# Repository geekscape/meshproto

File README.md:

meshproto
=========

MeshProto module: Hardware and software repository.

About:

Prototyping board with mounting points and pinouts to match MeshThing and MeshUSB.

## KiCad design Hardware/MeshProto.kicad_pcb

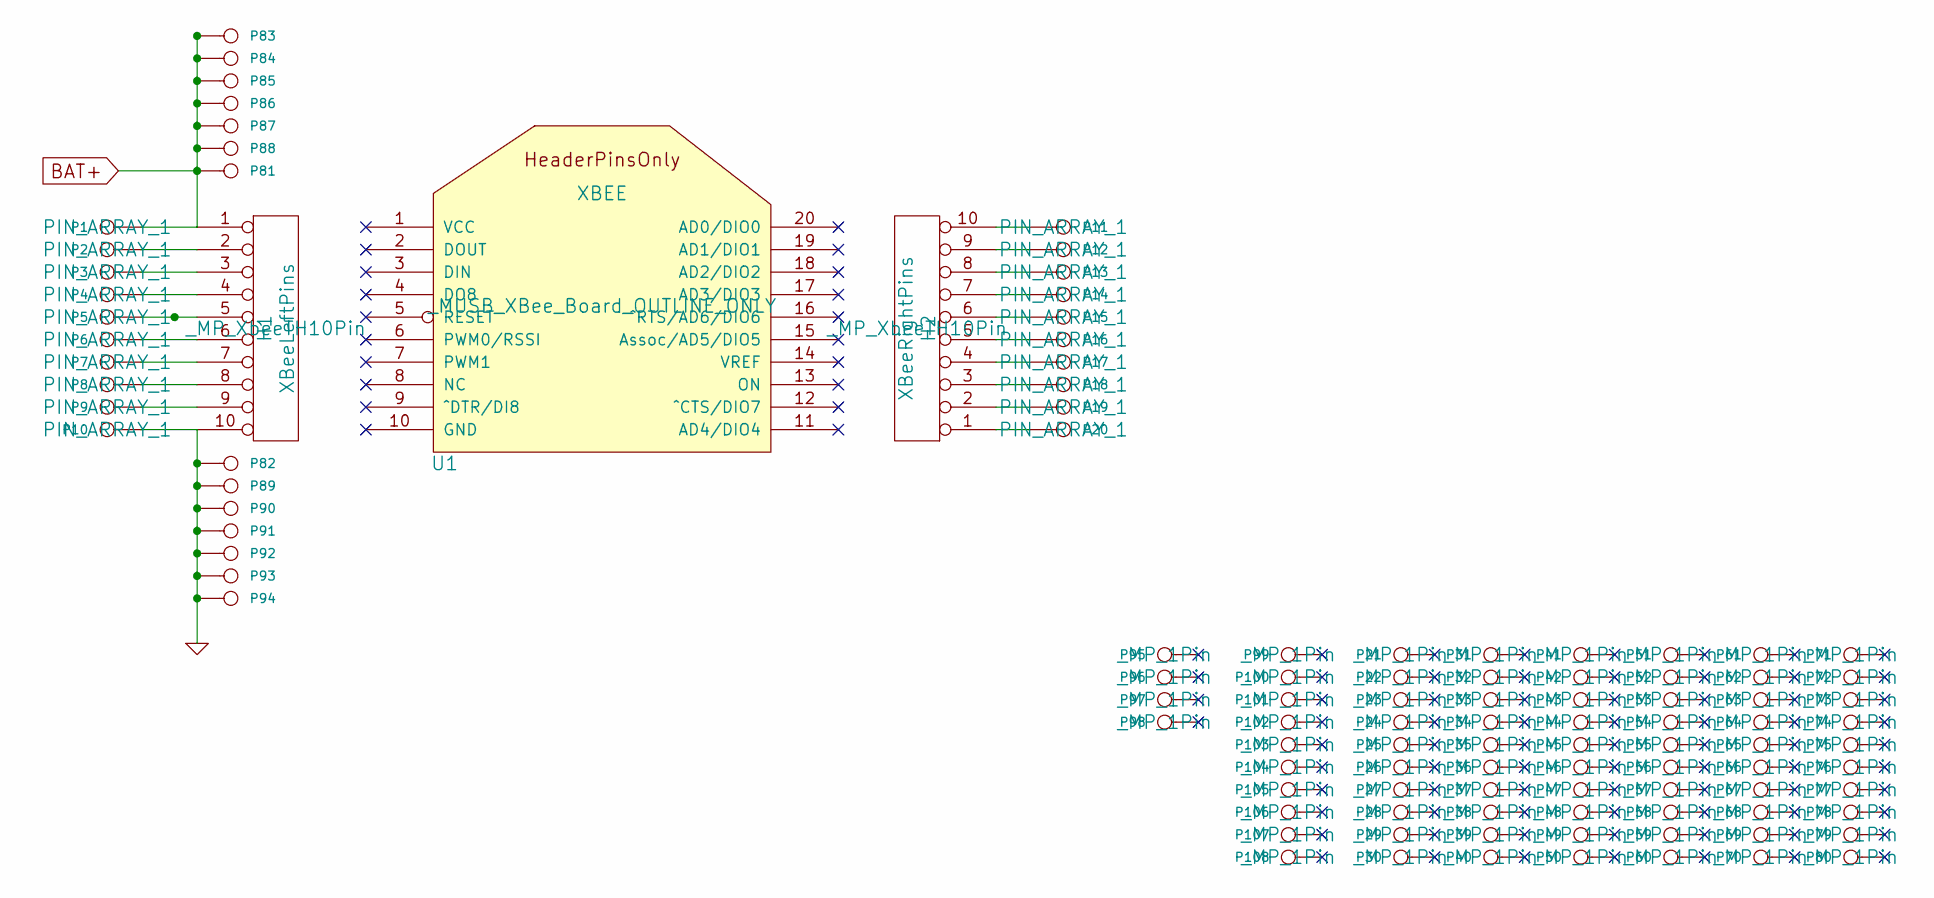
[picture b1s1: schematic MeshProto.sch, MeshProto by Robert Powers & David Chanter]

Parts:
H1: XBeeLeftPins; _MP_XbeeTH10Pin
H2: XBeeRightPins; _MP_XbeeTH10Pin
P1, P2, P3, P4, P5, P6, P7, P8, P9, P10, P11, P12, P13, P14, P15, P16, P17, P18, P19, P20: CONN_1; PIN_ARRAY_1
P21, P22, P23, P24, P25, P26, P27, P28, P29, P30, P31, P32, P33, P34, P35, P36, P37, P38, P39, P40, P41, P42, P43, P44, P45, P46, P47, P48, P49, P50, P51, P52, P53, P54, P55, P56, P57, P58, P59, P60, P61, P62, P63, P64, P65, P66, P67, P68, P69, P70, P71, P72, P73, P74, P75, P76, P77, P78, P79, P80, P95, P96, P97, P98, P99, P100, P101, P102, P103, P104, P105, P106, P107, P108: CONN_1; _MP_1Pin
P81, P82, P83, P84, P85, P86, P87, P88, P89, P90, P91, P92, P93, P94: CONN_1
U1: XBEE; _MUSB_XBee_Board_OUTLINE_ONLY

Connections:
BAT+: H1.1, P1.1, P81.1, P83.1, P84.1, P85.1, P86.1, P87.1, P88.1
GND: H1.10, P10.1, P82.1, P89.1, P90.1, P91.1, P92.1, P93.1, P94.1
unnamed: H1.2, P2.1
unnamed: H1.3, P3.1
unnamed: H1.4, P4.1
unnamed: H1.5, P5.1
unnamed: H1.6, P6.1
unnamed: H1.7, P7.1
unnamed: H1.8, P8.1
unnamed: H1.9, P9.1
unnamed: H2.1, P20.1
unnamed: H2.2, P19.1
unnamed: H2.3, P18.1
unnamed: H2.4, P17.1
unnamed: H2.5, P16.1
unnamed: H2.6, P15.1
unnamed: H2.7, P14.1
unnamed: H2.8, P13.1
unnamed: H2.9, P12.1
unnamed: H2.10, P11.1

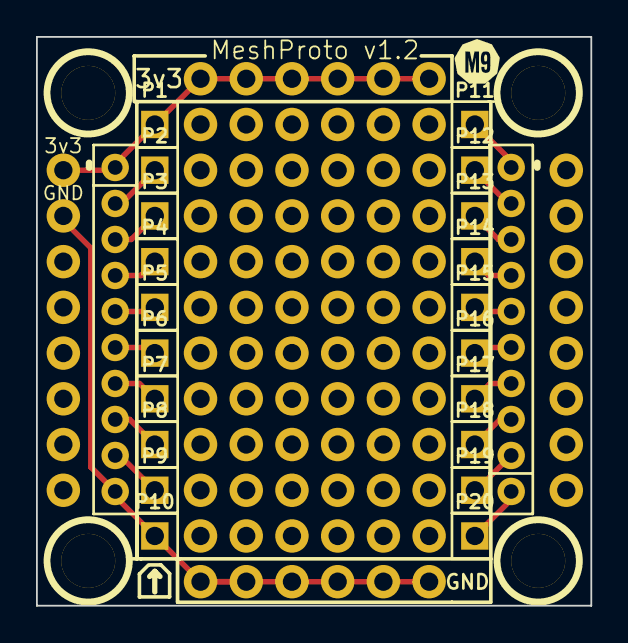
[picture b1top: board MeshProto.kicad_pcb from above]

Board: 2 copper layers, 30.8 x 31.6 mm, 117 parts (0 on the bottom side), 20 nets.

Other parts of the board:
1PIN1, 1PIN2, 1PIN3, 1PIN4: P***; _MP_MountingHole
VAL: M9Logo-2mm; M9Logo-scaled
VAL#2: M9Logo-2mm; M9Logo-scaled

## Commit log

2013-10-25 Woot v01
2013-11-12 Layout Almost Complete
2013-11-12 Added labels
    Added GND and BAT+ labels to silkscreen.
2013-11-12 Totally Wired Up
2013-11-12 Looks Nice
2013-11-14 Add backup files "*~" to the ignore list.
2013-11-20 Removed redundant MeshUSB files.
    Cleaned up repo, added picture
2013-11-21 Increased track width. Routed GND on back to move it away from the board edge.
2013-11-21 Added OSHW logo, cleaned up libs.
2013-11-22 Further minor changes.
2013-11-27 Cleaned up silk, added license.
2013-11-27 Adjust back silk - kicad display bug? Gerbers.
2013-11-28 Widened board by 0.5mm to fit everything better. Changed some silks.
2013-12-05 v1.1 initial changes. Increased drill size, changed libs, back silk larger.
2013-12-05 TAPR Hardware License added.
2013-12-06 Bump silk version to v1.1.
2014-02-27 Initial changes to v1.2.
2014-02-27 Final changes, silks, logo, gerbers.
2014-03-06 V0.3 production files.

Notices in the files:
Hardware/MeshProto.kicad_pcb:
©M9Design.co 2013
